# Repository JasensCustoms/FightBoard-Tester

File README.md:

# FightBoard-Tester
A Simple Design to Test common form factor fighting boards. This connects directly across the common 20 pin header as well as the JST PH-5 and PH-4 connectors for common connectors. Each possible button input is on a dipswitch connecting GROUND to the signal in order to test behaviors on boot in any combination required. Ideally, the LEDs for the corresponding input, light up as well when the dipswitch is in the "ON" position indicating a button is held down.

From left to right, as indicated on the board, there are three dipswitch banks:

First: U, D, L, R
Second: P1, P2, P3, P4
Third:  K1, K2, K3, K4
Fourth: START, SELECT, HOME, TP CLICK
Fifth: L3, R3. The final two positions are unconnected.

The momentary switch is a turbo button. Id didn't make sense to include it as a dipswitch as that's not a potential use case in real life.

Player LEDs and Turbo LED functions such that they always have 3V applied, but are turned on when the corresponding pin on the fight board is sent low. This is a common way to drive these LEDs and Brook has done it for years. The PS360+ that preceeded most of the newer boards did it this way as well. Always confirm these details before connecting things.

The JST connectors are "reversed" from those on the fighting board so you would connect Pin 1 to Pin 5, Pin 2 to Pin 4, Pin 3 to Pin 3, Pin 4 to Pin 2, and Pin 5 to Pin 1. This look slike wires are directly connected between the PCBs in a straight line. 

As of 2.4.25 - this is an untested design.

# License

This design is licensed under CC-NC-BY-SA-4.0. Details can be found here: https://creativecommons.org/licenses/by-nc-sa/4.0/deed.en

You are free to:
Share — copy and redistribute the material in any medium or format
Adapt — remix, transform, and build upon the material

The licensor cannot revoke these freedoms as long as you follow the license terms.

Under the following terms:
*Attribution — You must give appropriate credit , provide a link to the license, and indicate if changes were made . You may do so in any reasonable manner, but not in any way that suggests the licensor endorses you or your use.
*NonCommercial — You may not use the material for commercial purposes .
*ShareAlike — If you remix, transform, or build upon the material, you must distribute your contributions under the same license as the original.
No additional restrictions — You may not apply legal terms or technological measures that legally restrict others from doing anything the license permits.

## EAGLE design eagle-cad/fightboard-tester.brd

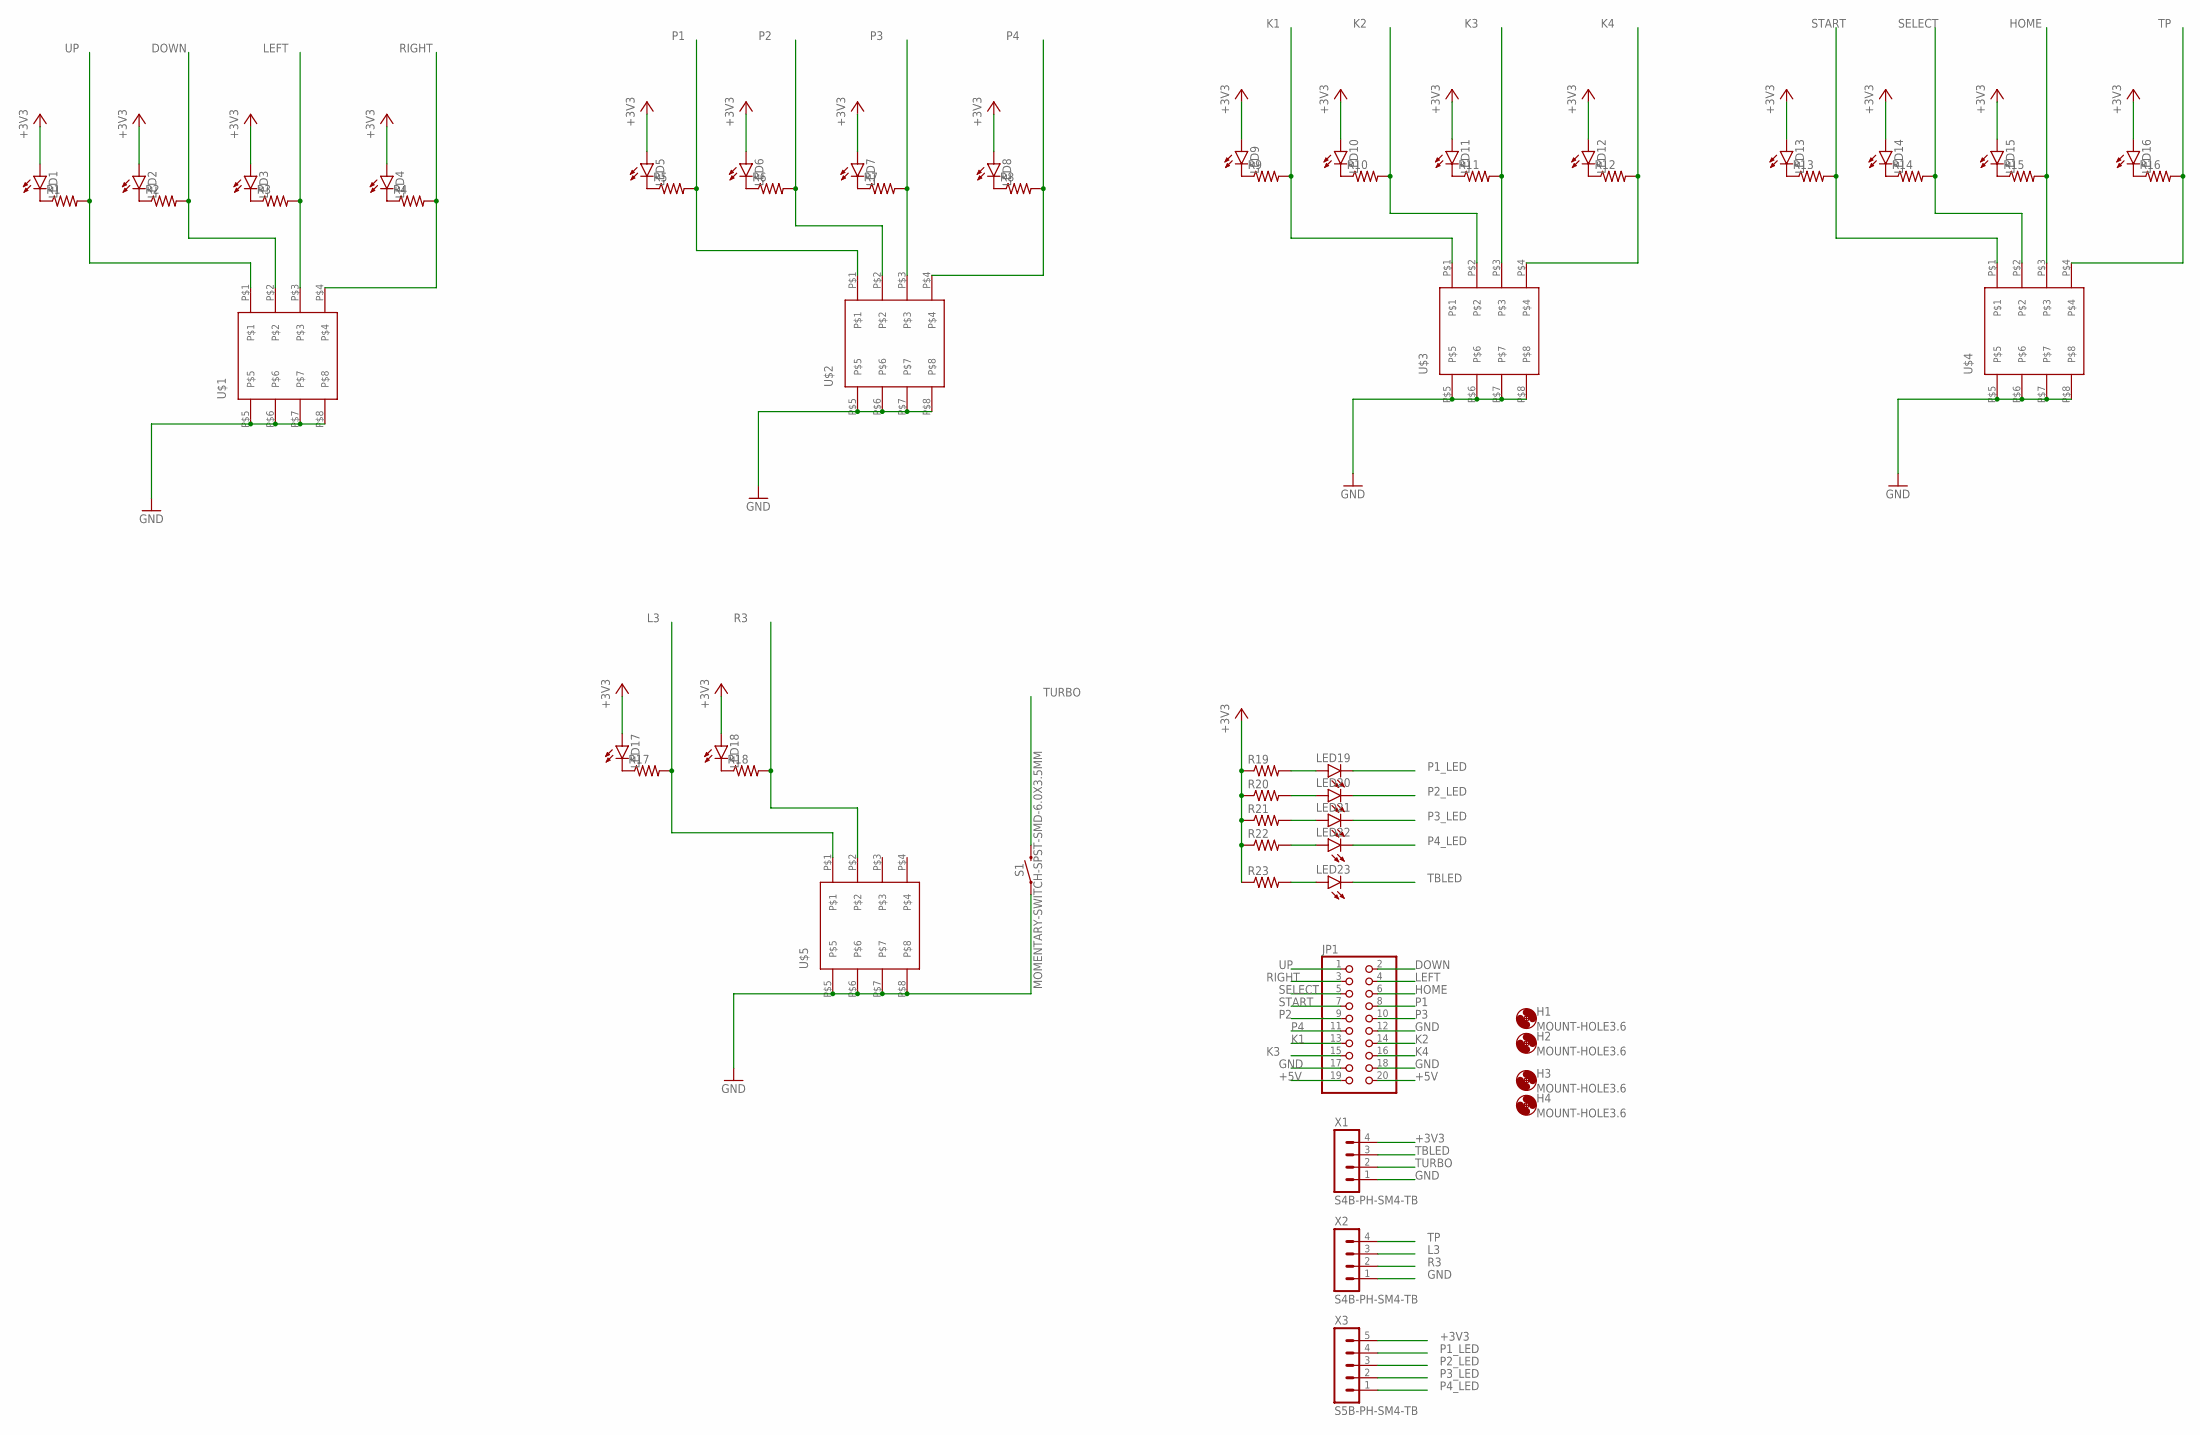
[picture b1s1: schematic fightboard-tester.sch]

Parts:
H1, H2, H3, H4: MOUNT-HOLE3.6; 3,6
JP1: PINHD-2X10; 2X10
LED1, LED2, LED3, LED4, LED5, LED6, LED7, LED8, LED9, LED10, LED11, LED12, LED13, LED14, LED15, LED16, LED17, LED18, LED19, LED20, LED21, LED22, LED23: LEDCHIPLED_0805; CHIPLED_0805
R1, R2, R3, R4, R5, R6, R7, R8, R9, R10, R11, R12, R13, R14, R15, R16, R17, R18, R19, R20, R21, R22, R23: R-US_R0805; R0805
S1: MOMENTARY-SWITCH-SPST-SMD-6.0X3.5MM; TACTILE_SWITCH_SMD_6.0X3.5MM
U$1, U$2, U$3, U$4, U$5: DSIC04LS
X1, X2: S4B-PH-SM4-TB
X3: S5B-PH-SM4-TB

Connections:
+3V3: LED1.A, LED2.A, LED3.A, LED4.A, LED5.A, LED6.A, LED7.A, LED8.A, LED9.A, LED10.A, LED11.A, LED12.A, LED13.A, LED14.A, LED15.A, LED16.A, LED17.A, LED18.A, R19.1, R20.1, R21.1, R22.1, R23.1, X1.4, X3.5
+5V: JP1.19, JP1.20
DOWN: JP1.2, R2.2, U$1.P$2
GND: JP1.12, JP1.17, JP1.18, S1.1, U$1.P$5, U$1.P$6, U$1.P$7, U$1.P$8, U$2.P$5, U$2.P$6, U$2.P$7, U$2.P$8, U$3.P$5, U$3.P$6, U$3.P$7, U$3.P$8, U$4.P$5, U$4.P$6, U$4.P$7, U$4.P$8, U$5.P$5, U$5.P$6, U$5.P$7, U$5.P$8, X1.1, X2.1
HOME: JP1.6, R15.2, U$4.P$3
K1: JP1.13, R9.2, U$3.P$1
K2: JP1.14, R10.2, U$3.P$2
K3: JP1.15, R11.2, U$3.P$3
K4: JP1.16, R12.2, U$3.P$4
L3: R17.2, U$5.P$1, X2.3
LEFT: JP1.4, R3.2, U$1.P$3
unnamed: LED5.C, R5.1
unnamed: LED6.C, R6.1
unnamed: LED7.C, R7.1
unnamed: LED8.C, R8.1
unnamed: LED1.C, R1.1
unnamed: LED2.C, R2.1
unnamed: LED3.C, R3.1
unnamed: LED4.C, R4.1
unnamed: LED9.C, R9.1
unnamed: LED10.C, R10.1
unnamed: LED11.C, R11.1
unnamed: LED12.C, R12.1
unnamed: LED13.C, R13.1
unnamed: LED14.C, R14.1
unnamed: LED15.C, R15.1
unnamed: LED16.C, R16.1
unnamed: LED17.C, R17.1
unnamed: LED18.C, R18.1
unnamed: LED19.A, R19.2
unnamed: LED20.A, R20.2
unnamed: LED21.A, R21.2
unnamed: LED22.A, R22.2
unnamed: LED23.A, R23.2
P1: JP1.8, R5.2, U$2.P$1
P1_LED: LED19.C, X3.4
P2: JP1.9, R6.2, U$2.P$2
P2_LED: LED20.C, X3.3
P3: JP1.10, R7.2, U$2.P$3
P3_LED: LED21.C, X3.2
P4: JP1.11, R8.2, U$2.P$4
P4_LED: LED22.C, X3.1
R3: R18.2, U$5.P$2, X2.2
RIGHT: JP1.3, R4.2, U$1.P$4
SELECT: JP1.5, R14.2, U$4.P$2
START: JP1.7, R13.2, U$4.P$1
TBLED: LED23.C, X1.3
TP: R16.2, U$4.P$4, X2.4
TURBO: S1.2, X1.2
UP: JP1.1, R1.2, U$1.P$1

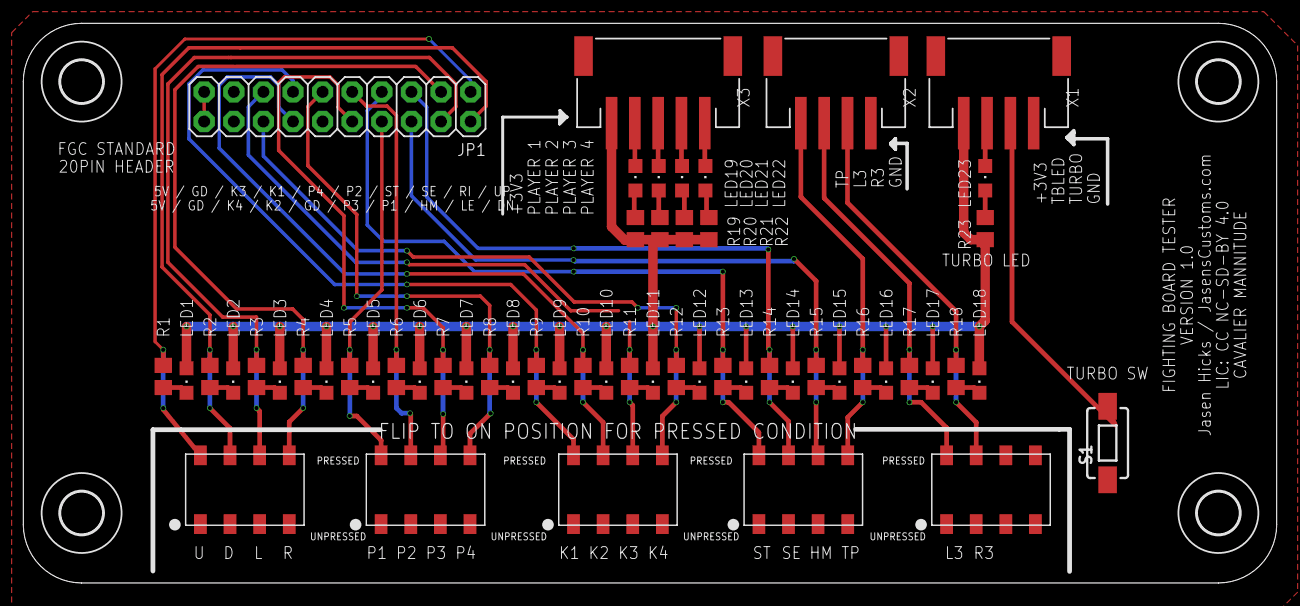
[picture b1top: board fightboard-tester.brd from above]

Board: 2 copper layers, 107.5 x 48.0 mm, 60 parts (0 on the bottom side), 50 nets.

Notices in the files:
parts and their libraries:
3Ded-SparkFun-Switches: Licensing: Creative Commons ShareAlike 4.0 International - https://creativecommons.org/licenses/by-sa/4.0
